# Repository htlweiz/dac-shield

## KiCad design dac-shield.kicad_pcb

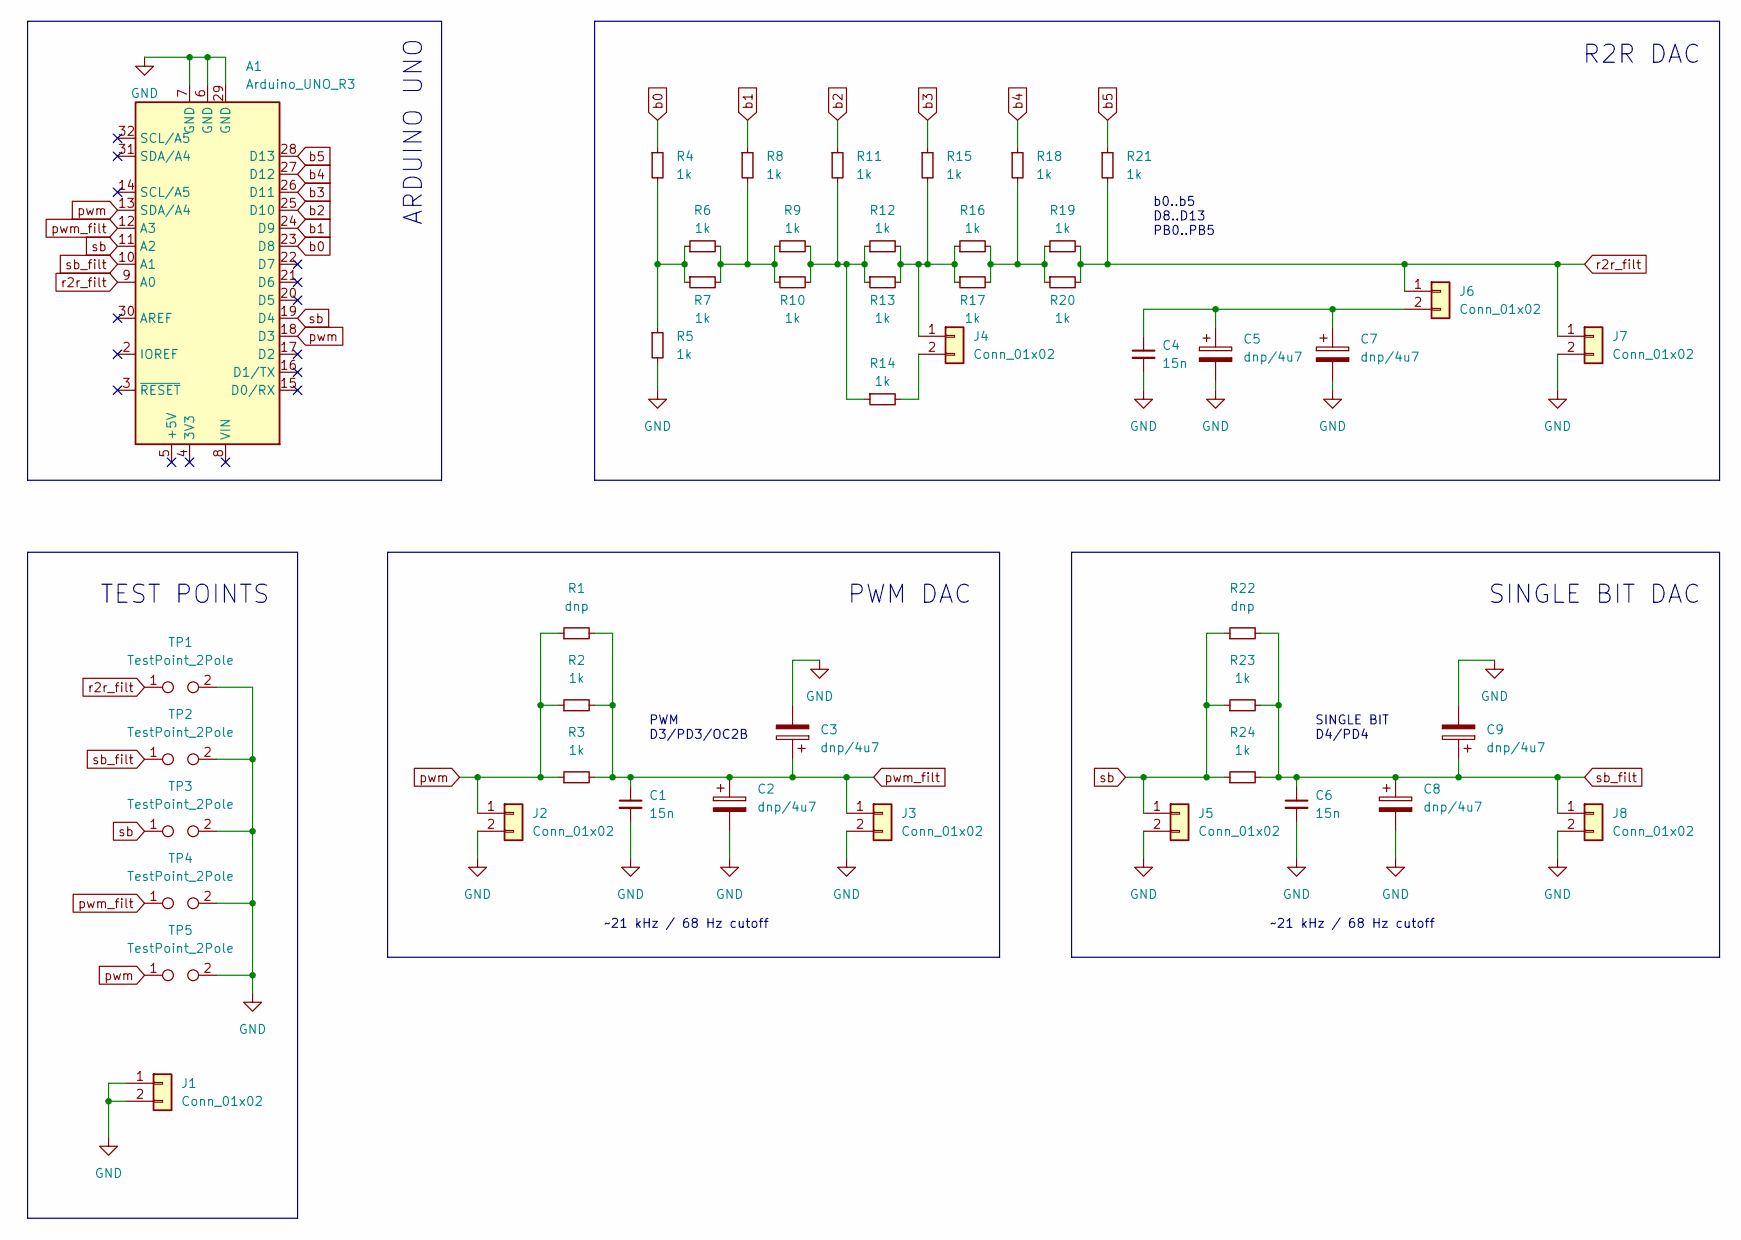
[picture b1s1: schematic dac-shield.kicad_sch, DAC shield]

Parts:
A1: Arduino_UNO_R3
C1, C4, C6: 15n; C_0603_1608Metric
C2, C5, C8: dnp/4u7; CP_Radial_D10.0mm_P5.00mm_P7.50mm
C3, C7, C9: dnp/4u7; CP_Radial_D5.0mm_P2.50mm
J1, J2, J3, J4, J5, J6, J7, J8: Conn_01x02; PinHeader_1x02_P2.54mm_Vertical
R1, R22: dnp; R_Axial_DIN0207_L6.3mm_D2.5mm_P10.16mm_Horizontal
R2, R3, R4, R5, R6, R7, R8, R9, R10, R11, R12, R13, R14, R15, R16, R17, R18, R19, R20, R21, R23, R24: 1k; R_0402_1005Metric
TP1, TP2, TP3, TP4, TP5: TestPoint_2Pole; PinHeader_1x02_P2.54mm_Vertical

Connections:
GND: A1.6 (GND), A1.7 (GND), A1.29 (GND), C1.2, C2.2, C3.2, C4.2, C5.2, C6.2, C7.2, C8.2, C9.2, J1.1, J1.2, J2.2, J3.2, J5.2, J7.2, J8.2, R5.2, TP1.2, TP2.2, TP3.2, TP4.2, TP5.2
unnamed: C4.1, C5.1, C7.1, J6.2
unnamed: J4.1, R12.2, R13.2, R15.2, R16.1, R17.1
unnamed: J4.2, R14.2
unnamed: R4.2, R5.1, R6.1, R7.1
unnamed: R6.2, R7.2, R8.2, R9.1, R10.1
unnamed: R9.2, R10.2, R11.2, R12.1, R13.1, R14.1
unnamed: R16.2, R17.2, R18.2, R19.1, R20.1
b0: A1.23 (D8), R4.1
b1: A1.24 (D9), R8.1
b2: A1.25 (D10), R11.1
b3: A1.26 (D11), R15.1
b4: A1.27 (D12), R18.1
b5: A1.28 (D13), R21.1
pwm: A1.13 (SDA/A4), A1.18 (D3), J2.1, R1.1, R2.1, R3.1, TP5.1
pwm_filt: A1.12 (A3), C1.1, C2.1, C3.1, J3.1, R1.2, R2.2, R3.2, TP4.1
r2r_filt: A1.9 (A0), J6.1, J7.1, R19.2, R20.2, R21.2, TP1.1
sb: A1.11 (A2), A1.19 (D4), J5.1, R22.1, R23.1, R24.1, TP3.1
sb_filt: A1.10 (A1), C6.1, C8.1, C9.1, J8.1, R22.2, R23.2, R24.2, TP2.1

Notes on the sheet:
b0..b5 D8..D13 PB0..PB5
PWM D3/PD3/OC2B
~21 kHz / 68 Hz cutoff
R2R DAC
PWM DAC
SINGLE BIT D4/PD4
SINGLE BIT DAC
ARDUINO UNO
TEST POINTS

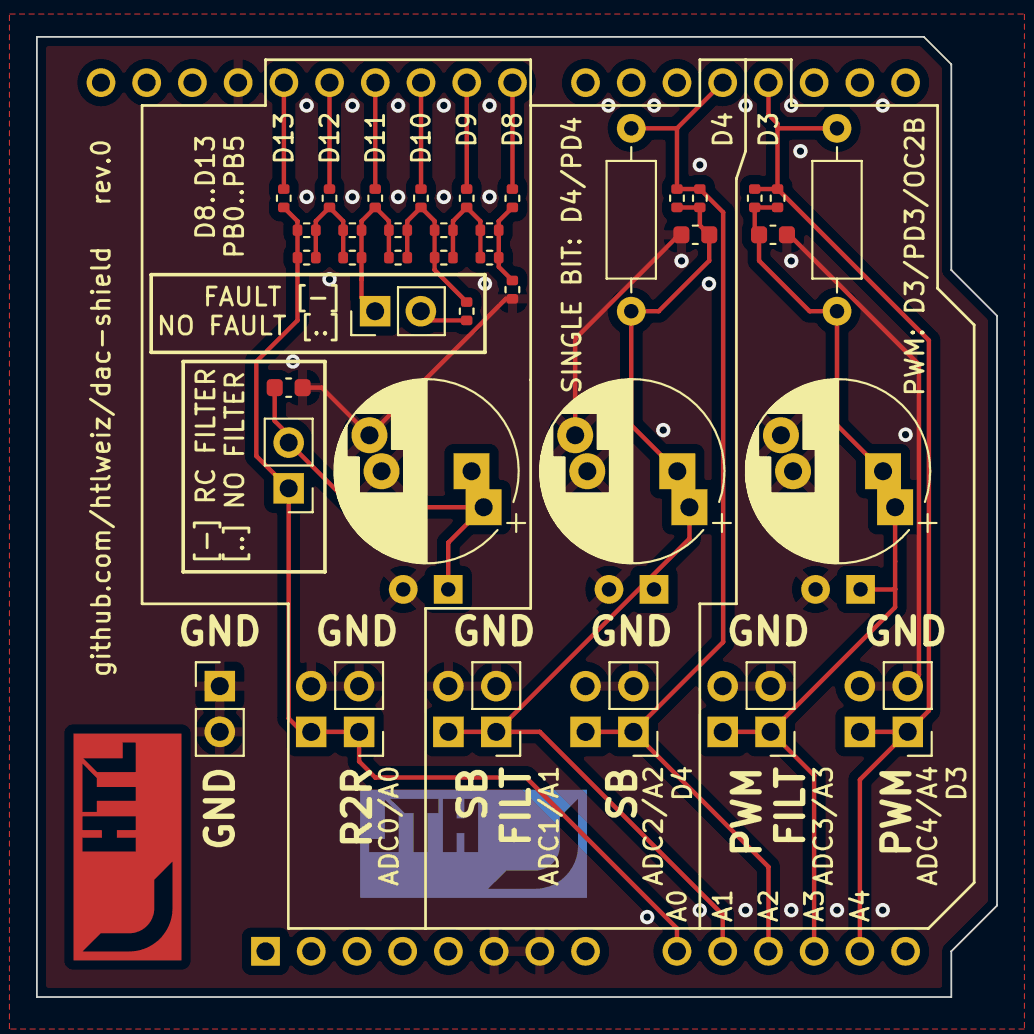
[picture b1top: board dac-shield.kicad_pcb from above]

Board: 2 copper layers, 53.3 x 53.3 mm, 47 parts (1 on the bottom side), 19 nets.

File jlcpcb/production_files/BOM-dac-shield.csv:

Comment,Designator,Footprint,LCSC
1k,"R10,R11,R12,R13,R14,R16,R17,R18,R19,R2,R20,R21,R23,R24,R3,R4,R5,R6,R7,R8,R9",R_0402_1005Metric,C11702
dnp,R22,R_Axial_DIN0207_L6.3mm_D2.5mm_P10.16mm_Horizontal,
1k,R15,R_0402_1005Metric,
dnp,R1,R_Axial_DIN0207_L6.3mm_D2.5mm_P10.16mm_Horizontal,
Conn_01x02,J7,PinHeader_1x02_P2.54mm_Vertical,
Conn_01x02,J6,PinHeader_1x02_P2.54mm_Vertical,
Conn_01x02,J5,PinHeader_1x02_P2.54mm_Vertical,
Conn_01x02,J4,PinHeader_1x02_P2.54mm_Vertical,
Conn_01x02,J3,PinHeader_1x02_P2.54mm_Vertical,
Conn_01x02,J2,PinHeader_1x02_P2.54mm_Vertical,
Conn_01x02,J1,PinHeader_1x02_P2.54mm_Vertical,
15n,C6,C_0603_1608Metric,
dnp/4u7,C5,CP_Radial_D10.0mm_P5.00mm_P7.50mm,
15n,C4,C_0603_1608Metric,
dnp/4u7,C3,CP_Radial_D5.0mm_P2.50mm,
dnp/4u7,C2,CP_Radial_D10.0mm_P5.00mm_P7.50mm,
15n,C1,C_0603_1608Metric,
Arduino_UNO_R3,A1,Arduino_UNO_R3,
Conn_01x02,J8,PinHeader_1x02_P2.54mm_Vertical,
TestPoint_2Pole,TP5,PinHeader_1x02_P2.54mm_Vertical,
TestPoint_2Pole,TP4,PinHeader_1x02_P2.54mm_Vertical,
TestPoint_2Pole,TP3,PinHeader_1x02_P2.54mm_Vertical,
TestPoint_2Pole,TP2,PinHeader_1x02_P2.54mm_Vertical,
TestPoint_2Pole,TP1,PinHeader_1x02_P2.54mm_Vertical,
dnp/4u7,C9,CP_Radial_D5.0mm_P2.50mm,
dnp/4u7,C7,CP_Radial_D5.0mm_P2.50mm,
dnp/4u7,C8,CP_Radial_D10.0mm_P5.00mm_P7.50mm,

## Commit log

2023-02-16 modified silkscreen
2023-02-16 fixed cap value and added annotations
2023-02-16 added analog feedback
2023-02-16 first layout draft
2023-02-16 first fab files
2023-02-16 added test program
2023-02-16 added test points, recreated fab files
2023-02-17 prettified things
2023-02-17 changed testpoint footprints
2023-02-17 updated fab files
2023-02-17 created footprint options
